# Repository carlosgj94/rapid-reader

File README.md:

# MOTIF

Embedded Rust firmware for an ESP32-S3 board with a Sharp LS027 memory LCD.

This repository is in a docs-first rebuild state.

Today:

- `src/bin/main.rs` is a minimal bring-up baseline
- `crates/ls027b7dh01` contains the reusable display driver primitives
- `crates/domain`, `crates/app-runtime`, `crates/services`, and `crates/platform-esp32s3` define
  the barebones architecture skeleton
- the baseline already includes the current embassy runtime split, encoder input handling,
  deep-sleep integration, internal flash storage, and boot-hydrated settings
- the new target architecture is documented under `docs/`

The runtime is intentionally thinner than the target system. The technical documentation is now the
source of truth for the rebuild direction.

## Start Here

- [`docs/index.md`](docs/index.md): documentation entrypoint and reading order
- [`docs/architecture/overview.md`](docs/architecture/overview.md): target architecture
- [`docs/flows/article-lifecycle.md`](docs/flows/article-lifecycle.md): end-to-end content flow
- [`docs/modules/provisioning.md`](docs/modules/provisioning.md): BLE-first onboarding model

## Build And Flash

The workspace defaults to `xtensa-esp32s3-none-elf` via `.cargo/config.toml`.
The Cargo runner now passes the Motif partition table and `16mb` flash size explicitly to
`espflash`, and `espflash.toml` keeps the same layout available for direct `espflash` commands.

Flash and monitor:

```bash
cargo run --release
```

Useful local checks:

```bash
cargo fmt --all
cargo check --offline
cargo clippy --offline --workspace --lib
```

## Hardware Docs

- [`docs/board-config.md`](docs/board-config.md): current GPIO wiring used by the stripped firmware
- [`docs/ls027-notes.md`](docs/ls027-notes.md): low-level LS027 protocol notes

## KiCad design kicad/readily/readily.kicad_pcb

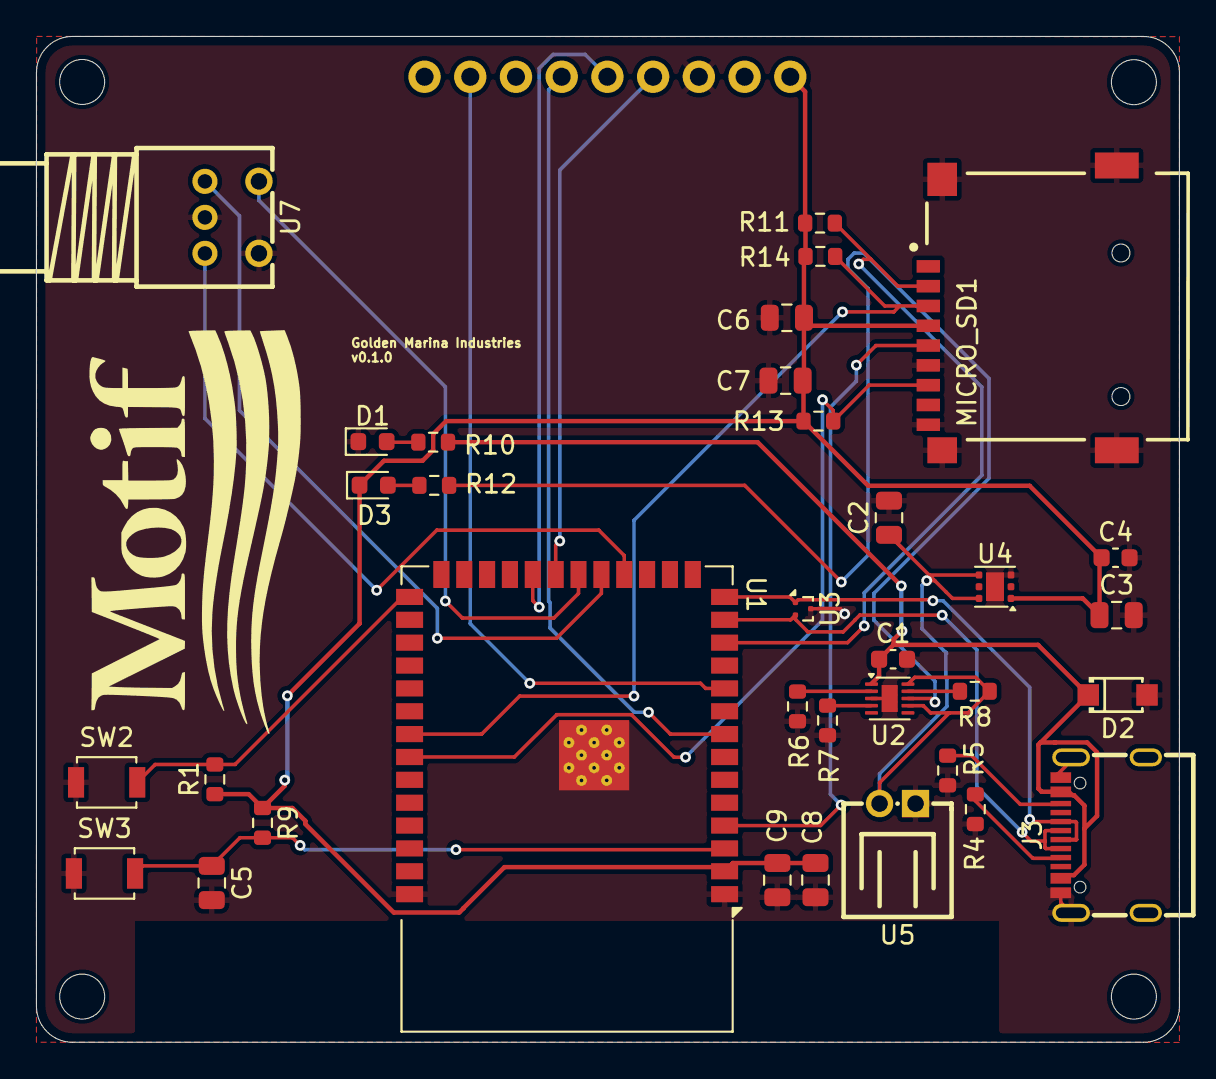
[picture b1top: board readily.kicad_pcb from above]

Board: 2 copper layers, 63.5 x 55.9 mm, 39 parts (0 on the bottom side), 27 nets.

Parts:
C1: 4.7uF; C_0603_1608Metric
C2: 22uF; C_0805_2012Metric
C3, C5, C9: 10uF; C_0805_2012Metric
C4: 100nF; C_0603_1608Metric
C6: 47uF; C_0805_2012Metric
C7, C8: 100nF; C_0805_2012Metric
D1: White LED; LED_0603_1608Metric
D2: SMF5_0A_C19077497
D3: LED White; LED_0603_1608Metric
J1: Conn_01x09_Socket; Pins01x09
J3: USB_C_Receptacle_USB2.0_16P; TYPE-C16PIN
MICRO_SD1: TF-01A
Mount1, Mount2, Mount3, Mount4: MountingHole_2.5mm
R1: 10K; R_0603_1608Metric
R4, R5: 5.1kΩ; R_0603_1608Metric
R6: 1kΩ; R_0603_1608Metric
R7: 2kΩ; R_0603_1608Metric
R8, R11, R13, R14: 10kΩ; R_0603_1608Metric
R9, R10: 5.1K; R_0603_1608Metric
R12: 2.2K; R_0603_1608Metric
SW2, SW3: SW_SPST; SW_SPST_B3U-1000P
U1: ESP32-S3-WROOM-1
U2: BQ24040DSQR; Texas_DSQ0010A_WSON-10-1EP_2x2mm_P0.4mm_EP0.9x1.5mm
U3: TPD2EUSB30; Texas_DRT-3
U4: TLV75533PDRV; WSON-6-1EP_2x2mm_P0.65mm_EP1x1.6mm
U5: WAFER-PH2_0-2PWZ
U7: ED08907M-FB15C7_0-C10-2049

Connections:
+3V3: C3.1, C4.1, C6.2, C7.2, C8.1, C9.1, D3.1 (K), J1.1, MICRO_SD1.4 (VDD), R1.1, R9.1, R11.2, R13.2, R14.2, U1.2 (3V3), U4.1 (OUT)
+5V: C1.1, D2.1 (K), J3.+5V, R10.1, U2.1 (IN)
BAT_CHG: R12.1, U2.8 (~CHG)
D+: J3.A6 (D+), J3.B6 (D+), U1.14 (USB_D+), U3.1 (D+)
D-: J3.A7 (D-), J3.B7 (D-), U1.13 (USB_D-), U3.2 (D-)
DISP_CLK: J1.4, U1.21 (IO13)
DISP_CS: J1.6, U1.8 (IO15)
DISP_DI: J1.5, U1.22 (IO14)
DISP_DISP: J1.8, U1.10 (IO17)
EN: C5.1, R9.2, SW3.2 (B), U1.3 (EN)
GND: C1.2, C2.2, C3.2, C4.2, C5.2, C6.1, C7.1, C8.2, C9.2, D1.1 (K), D2.2 (A), J1.3, J3.1, J3.2, J3.GND, MICRO_SD1.6 (VSS), MICRO_SD1.CD1 (CD), MICRO_SD1.MP1 (SHIELD), MICRO_SD1.MP2 (SHIELD), MICRO_SD1.MP3 (SHIELD), MICRO_SD1.MP4 (SHIELD), R4.1, R5.2, R6.1, R7.1, SW2.1 (A), SW3.1 (A), U1.1 (GND), U1.40 (GND), U1.41 (GND), U2.3 (VSS), U2.11 (EXP), U3.3 (GND), U4.3 (GND), U4.7 (GND), U5.1, U7.C, U7.S2
GPIO0: R1.2, SW2.2 (B), U1.27 (IO0)
unnamed: D1.2 (A), R10.2
unnamed: D3.2 (A), R12.2
unnamed: J3.A5 (CC1), R4.2
unnamed: J3.B5 (CC2), R5.1
unnamed: R6.2, U2.2 (ISET)
unnamed: R7.2, U2.4 (PRETERM)
unnamed: R8.2, U2.9 (TS)
RT_CLK: U1.18 (IO10), U7.A
RT_DT: U1.19 (IO11), U7.B
RT_SW: U1.20 (IO12), U7.S1
SD_CLK: MICRO_SD1.5 (CLK), U1.4 (IO4)
SD_CS: MICRO_SD1.2 (CD/DAT3), R11.1, U1.12 (IO8)
SD_MISO: MICRO_SD1.7 (DAT0), R13.1, U1.34 (IO41)
SD_MOSI: MICRO_SD1.3 (CMD), R14.1, U1.33 (IO40)
SYS_OUT: C2.1, R8.1, U2.7 (ISET2), U2.10 (OUT), U4.4 (EN), U4.6 (IN), U5.2

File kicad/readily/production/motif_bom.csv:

Designator,Footprint,Quantity,Value,LCSC Part #
C1,0603,1,4.7uF,C19666
C2,0805,1,22uF,C45783
"C3, C5, C9",0805,3,10uF,C15850
C4,0603,1,100nF,C14663
C6,0805,1,47uF,C76636
"C7, C8",0805,2,100nF,C49678
D1,0603,1,White LED,C2290
D2,SMF5_0A_C19077497,1,SMF5_0A_C19077497,C19077497
D3,0603,1,LED White,C2290
J3,TYPE-C16PIN,1,USB_C_Receptacle_USB2.0_16P,C393939
MICRO_SD1,TF-01A,1,TF-01A,
R1,0603,1,10K,C25804
"R10, R9",0603,2,5.1K,C23186
"R11, R13, R14, R8",0603,4,10kΩ,C25804
R12,0603,1,2.2K,C4190
"R4, R5",0603,2,5.1kΩ,C23186
R6,0603,1,1kΩ,C21190
R7,0603,1,2kΩ,C22975
"SW2, SW3",SW_SPST_B3U-1000P,2,SW_SPST,C720477
U1,ESP32-S3-WROOM-1,1,ESP32-S3-WROOM-1,
U2,Texas_DSQ0010A_WSON-10-1EP_2x2mm_P0.4mm_EP0.9x1.5mm,1,BQ24040DSQR,C81080
U3,Texas_DRT-3,1,TPD2EUSB30,
U4,WSON-6-1EP_2x2mm_P0.65mm_EP1x1.6mm,1,TLV75533PDRV,
U5,WAFER-PH2_0-2PWZ,1,WAFER-PH2_0-2PWZ,C5359610
U7,ED08907M-FB15C7_0-C10-2049,1,ED08907M-FB15C7_0-C10-2049,C18213496

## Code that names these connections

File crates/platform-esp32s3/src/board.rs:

pub const DISPLAY_CLK_GPIO: u8 = 13;
pub const DISPLAY_DI_GPIO: u8 = 14;
pub const DISPLAY_CS_GPIO: u8 = 15;
pub const DISPLAY_DISP_GPIO: u8 = 2;
pub const DISPLAY_EMD_GPIO: u8 = 9;

pub const SD_CS_GPIO: u8 = 8;
pub const SD_SCK_GPIO: u8 = 4;
pub const SD_MOSI_GPIO: u8 = 40;
pub const SD_MISO_GPIO: u8 = 41;

pub const ENCODER_CLK_GPIO: u8 = 10;
pub const ENCODER_DT_GPIO: u8 = 11;
pub const ENCODER_SW_GPIO: u8 = 12;
pub const SLEEP_WAKE_GPIO: u8 = ENCODER_SW_GPIO;

#[derive(Debug, Clone, Copy, Eq, PartialEq)]
pub struct BoardConfig {
    pub display_clk_gpio: u8,
    pub display_di_gpio: u8,
    pub display_cs_gpio: u8,
    pub display_disp_gpio: u8,
    pub display_emd_gpio: u8,
    pub sd_cs_gpio: u8,
    pub sd_sck_gpio: u8,
    pub sd_mosi_gpio: u8,
    pub sd_miso_gpio: u8,
    pub encoder_clk_gpio: u8,
    pub encoder_dt_gpio: u8,
    pub encoder_sw_gpio: u8,
    pub sleep_wake_gpio: u8,
}

impl BoardConfig {
    pub const fn new() -> Self {
        Self {
            display_clk_gpio: DISPLAY_CLK_GPIO,
            display_di_gpio: DISPLAY_DI_GPIO,
            display_cs_gpio: DISPLAY_CS_GPIO,
            display_disp_gpio: DISPLAY_DISP_GPIO,
            display_emd_gpio: DISPLAY_EMD_GPIO,
            sd_cs_gpio: SD_CS_GPIO,
            sd_sck_gpio: SD_SCK_GPIO,
            sd_mosi_gpio: SD_MOSI_GPIO,
            sd_miso_gpio: SD_MISO_GPIO,
            encoder_clk_gpio: ENCODER_CLK_GPIO,
            encoder_dt_gpio: ENCODER_DT_GPIO,
            encoder_sw_gpio: ENCODER_SW_GPIO,
            sleep_wake_gpio: SLEEP_WAKE_GPIO,
        }
    }
}

impl Default for BoardConfig {
    fn default() -> Self {
        Self::new()
    }
}

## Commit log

2026-02-09 feat: initial commit with the basic funcitonality
2026-02-09 feat: adding readme and agents
2026-02-12 feat: adding the sd card support and readying ebooks from it.
2026-02-12 fix: fixing some utf8 characters
2026-02-13 feat: updating the agents and readmy
2026-02-13 feat: refactor of the codebase
2026-02-13 feat: improving the parser reliability
2026-02-13 fix: showing the first chapter in the selection of chapters correctly
2026-02-13 feat: fixing some paragraphs rendering issue
2026-02-13 feat: adding sleep for the esp32
2026-02-13 feat: adding a loading screen
2026-02-13 feat: adding the database to index books and store progress on them
2026-02-13 fix: trying to fix the loading of chapters after a refresh
2026-02-13 fix: second attempt of fixing chapter loading
2026-02-16 feat: adding the kicad design
2026-02-17 feat: adding the first stage of the PCB
2026-02-17 fix: cleared out all DRC errors
2026-02-17 feat: adding vias and tracks to all components
2026-02-19 feat: updating the specs with the final rotatory encoder switch
2026-02-19 feat: version 1.0 of the pcb
2026-02-19 feat: adding the metadata
2026-03-11 feat: updating the screen position
2026-03-14 feat: creating the initial documentation
2026-03-14 feat: refactor to modularize the codebase further
2026-03-16 feat: adding logo to pcb, improving component placement and changing the battery connector to two pin JST
2026-03-16 feat: adding a GND plane to achieve higher power stability and heat management
2026-03-16 feat: finishing the power refactor on the board
2026-03-17 feat: updating and rerouting all components
2026-03-17 feat: switching the battery JST and generating the final files for next print
2026-03-31 feat: removing everything and set it to minimum
2026-03-31 feat: initial basics of the architecture
2026-03-31 feat: latest changes on the kicad schematics
2026-04-01 feat: adding sync between the theme and the settings
2026-04-01 chore: adding the documentation
2026-04-03 feat: adding wifi and backend support to the device
2026-04-03 feat: adding the loading of files
2026-04-03 feat: adding the loading of content
2026-04-03 chore: removing unneded files
2026-04-04 chore: improving network reliability with ip v4
2026-04-04 feat: increasing chunks of data per download
2026-04-04 feat: improving stability from article to article by poping out the cache
2026-04-04 feat: improving error handling timing on the network
2026-04-04 feat: changing endpoints to the new ones
2026-04-04 feat: improving speeds by not generating the TLS all the time.
2026-04-04 feat: improving the readability on the RSVP reading screen
2026-04-04 feat: better TLS handling, changing the content schema and better rendering of content
2026-04-04 feat: loading content by chunks and not the whole in a single batch
2026-04-04 chore: increasing the pauses
2026-04-04 feat: improving data readiness
2026-04-04 feat: making navigation in the RSVP view better
2026-04-04 feat: improving UI all around
2026-04-04 feat: improving the display responsiveness
2026-04-04 feat: improving the speed of the screen
2026-04-04 feat: improving the list rendering and animations
2026-04-04 feat: improving a bit the UI and animations of pause and paragraph view.
2026-04-04 chore: removing unneeded logs
2026-04-05 feat: massive network improvements
2026-04-05 feat: improving the batching speed
2026-04-05 feat: improving the reliability of queries
2026-04-05 feat: improving network reliability
2026-04-05 feat: docummenting the progress after all the reliability changes
2026-04-06 feat: switching the input on the RSVP view
2026-04-06 feat: improving startup connection
2026-04-06 feat: spi robustness
2026-04-06 feat: improving network speed
2026-04-07 Tune article transfers and restore failed fetch retries
2026-04-07 feat: UX improvements and rumping up the speed as the user reads
2026-04-07 feat: adding a loading indicator for the article downloading
2026-04-07 feat: adding motion to the articles loading screen
2026-04-08 feat: adding the for you screen
2026-04-08 feat: making list not loop
2026-04-08 feat: improving the UX
2026-04-08 feat: adding a splashscreen
